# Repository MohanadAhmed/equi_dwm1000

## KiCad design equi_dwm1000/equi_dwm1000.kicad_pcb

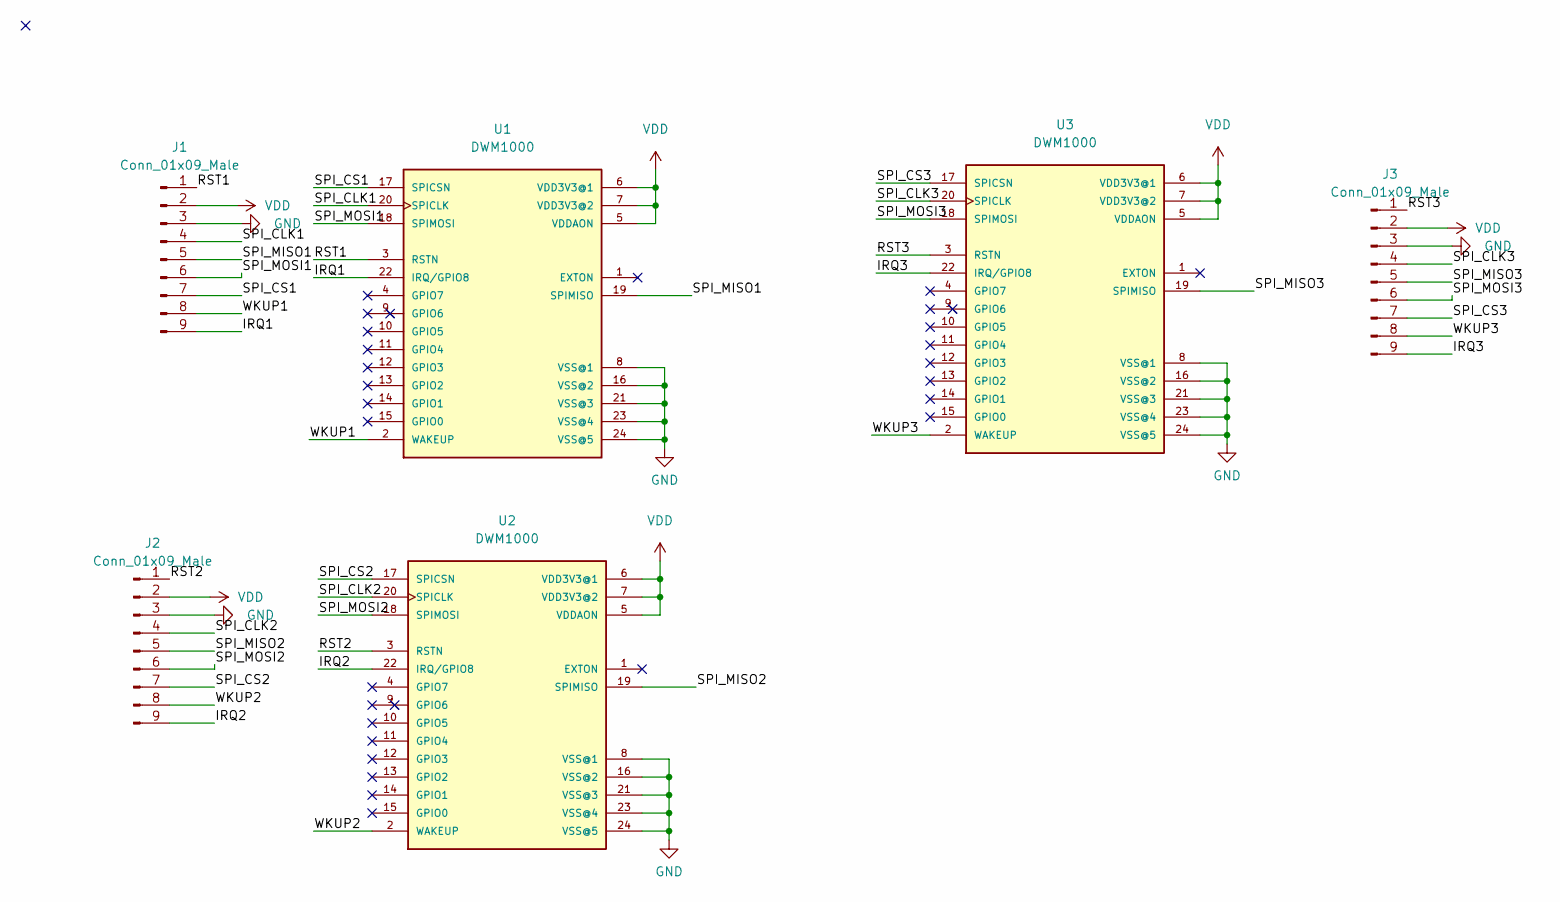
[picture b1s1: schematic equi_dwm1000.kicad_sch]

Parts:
J1, J2, J3: Conn_01x09_Male; PinHeader_1x09_P2.54mm_Vertical
U1, U2, U3: DWM1000

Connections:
/IRQ1: J1.9, U1.22 (IRQ/GPIO8)
/IRQ2: J2.9, U2.22 (IRQ/GPIO8)
/IRQ3: J3.9, U3.22 (IRQ/GPIO8)
/RST1: J1.1, U1.3 (RSTN)
/RST2: J2.1, U2.3 (RSTN)
/RST3: J3.1, U3.3 (RSTN)
/SPI_CLK1: J1.4, U1.20 (SPICLK)
/SPI_CLK2: J2.4, U2.20 (SPICLK)
/SPI_CLK3: J3.4, U3.20 (SPICLK)
/SPI_CS1: J1.7, U1.17 (SPICSN)
/SPI_CS2: J2.7, U2.17 (SPICSN)
/SPI_CS3: J3.7, U3.17 (SPICSN)
/SPI_MISO1: J1.5, U1.19 (SPIMISO)
/SPI_MISO2: J2.5, U2.19 (SPIMISO)
/SPI_MISO3: J3.5, U3.19 (SPIMISO)
/SPI_MOSI1: J1.6, U1.18 (SPIMOSI)
/SPI_MOSI2: J2.6, U2.18 (SPIMOSI)
/SPI_MOSI3: J3.6, U3.18 (SPIMOSI)
/WKUP1: J1.8, U1.2 (WAKEUP)
/WKUP2: J2.8, U2.2 (WAKEUP)
/WKUP3: J3.8, U3.2 (WAKEUP)
GND: J1.3, J2.3, J3.3, U1.8 (VSS@1), U1.16 (VSS@2), U1.21 (VSS@3), U1.23 (VSS@4), U1.24 (VSS@5), U2.8 (VSS@1), U2.16 (VSS@2), U2.21 (VSS@3), U2.23 (VSS@4), U2.24 (VSS@5), U3.8 (VSS@1), U3.16 (VSS@2), U3.21 (VSS@3), U3.23 (VSS@4), U3.24 (VSS@5)
VDD: J1.2, J2.2, J3.2, U1.5 (VDDAON), U1.6 (VDD3V3@1), U1.7 (VDD3V3@2), U2.5 (VDDAON), U2.6 (VDD3V3@1), U2.7 (VDD3V3@2), U3.5 (VDDAON), U3.6 (VDD3V3@1), U3.7 (VDD3V3@2)

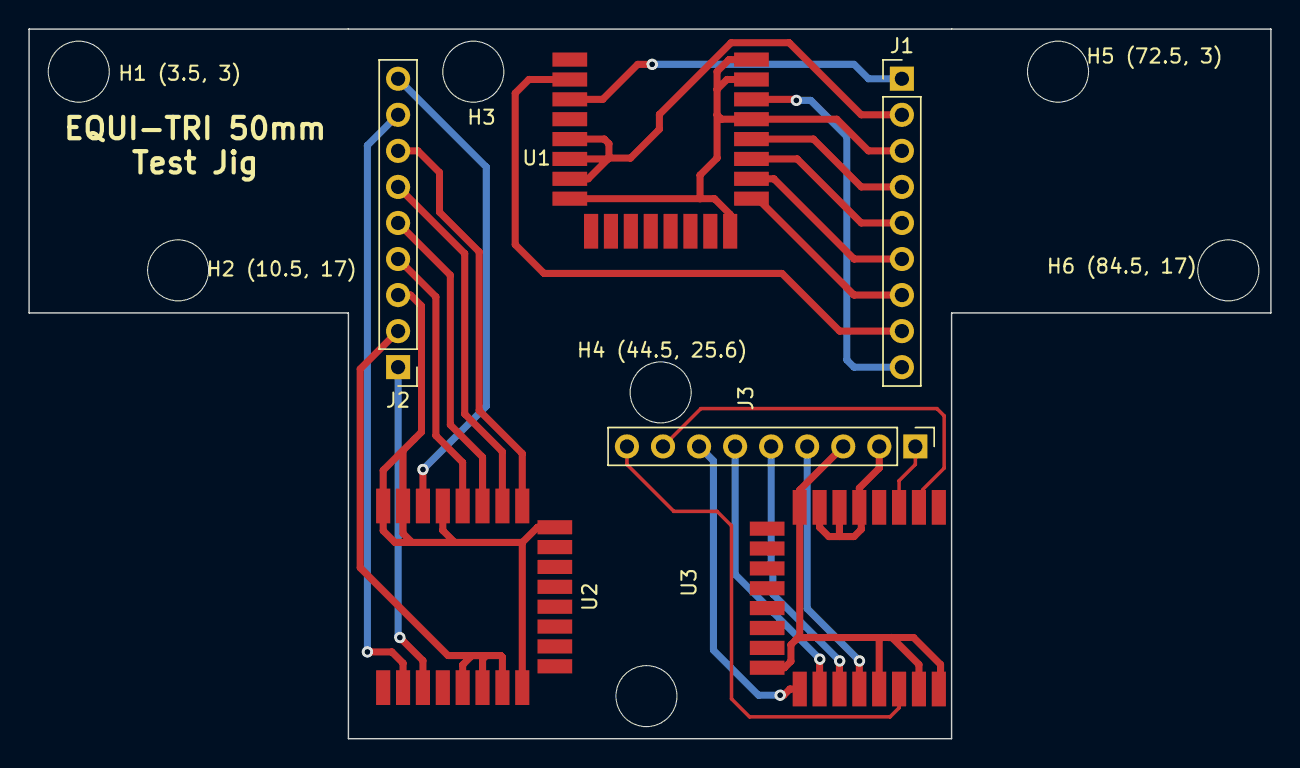
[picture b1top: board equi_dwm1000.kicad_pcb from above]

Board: 2 copper layers, 87.5 x 50.0 mm, 6 parts (0 on the bottom side), 23 nets.

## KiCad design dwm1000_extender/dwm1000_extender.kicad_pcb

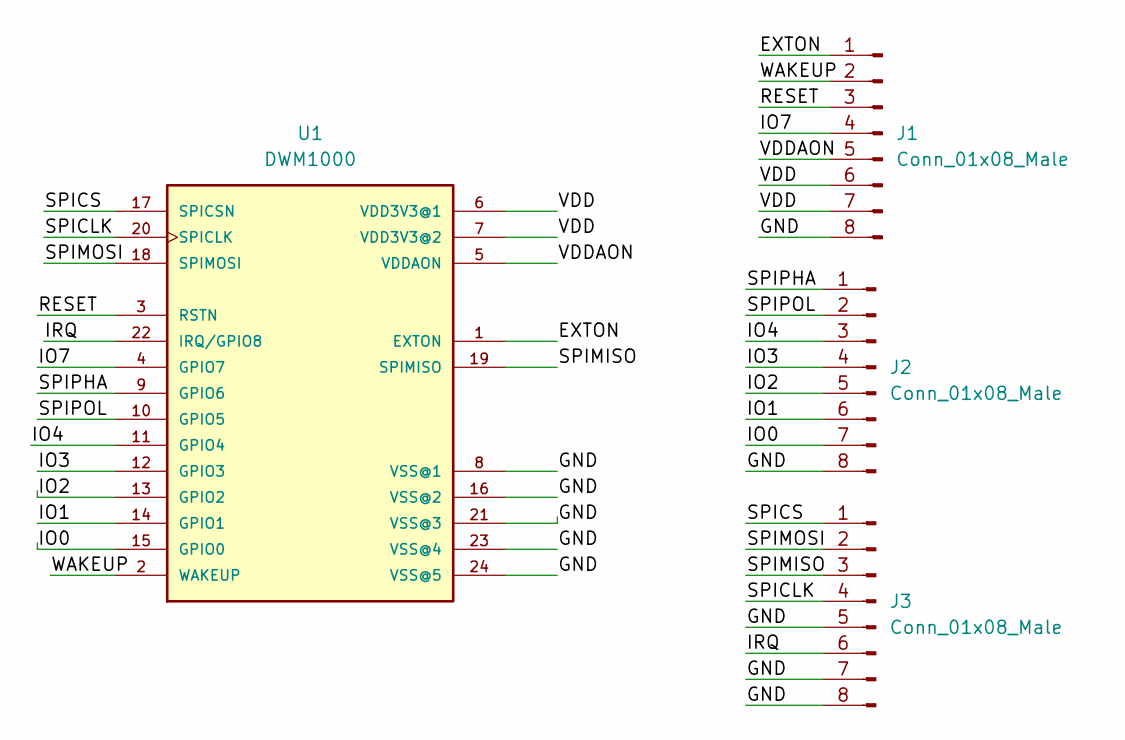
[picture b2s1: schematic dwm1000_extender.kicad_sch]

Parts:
J1, J2, J3: Conn_01x08_Male; PinHeader_1x08_P2.54mm_Vertical
U1: DWM1000

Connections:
/EXTON: J1.1, U1.1 (EXTON)
/GND: J1.8, J2.8, J3.5, J3.7, J3.8, U1.8 (VSS@1), U1.16 (VSS@2), U1.21 (VSS@3), U1.23 (VSS@4), U1.24 (VSS@5)
/IO0: J2.7, U1.15 (GPIO0)
/IO1: J2.6, U1.14 (GPIO1)
/IO2: J2.5, U1.13 (GPIO2)
/IO3: J2.4, U1.12 (GPIO3)
/IO4: J2.3, U1.11 (GPIO4)
/IO7: J1.4, U1.4 (GPIO7)
/IRQ: J3.6, U1.22 (IRQ/GPIO8)
/RESET: J1.3, U1.3 (RSTN)
/SPICLK: J3.4, U1.20 (SPICLK)
/SPICS: J3.1, U1.17 (SPICSN)
/SPIMISO: J3.3, U1.19 (SPIMISO)
/SPIMOSI: J3.2, U1.18 (SPIMOSI)
/SPIPHA: J2.1, U1.9 (GPIO6)
/SPIPOL: J2.2, U1.10 (GPIO5)
/VDD: J1.6, J1.7, U1.6 (VDD3V3@1), U1.7 (VDD3V3@2)
/VDDAON: J1.5, U1.5 (VDDAON)
/WAKEUP: J1.2, U1.2 (WAKEUP)

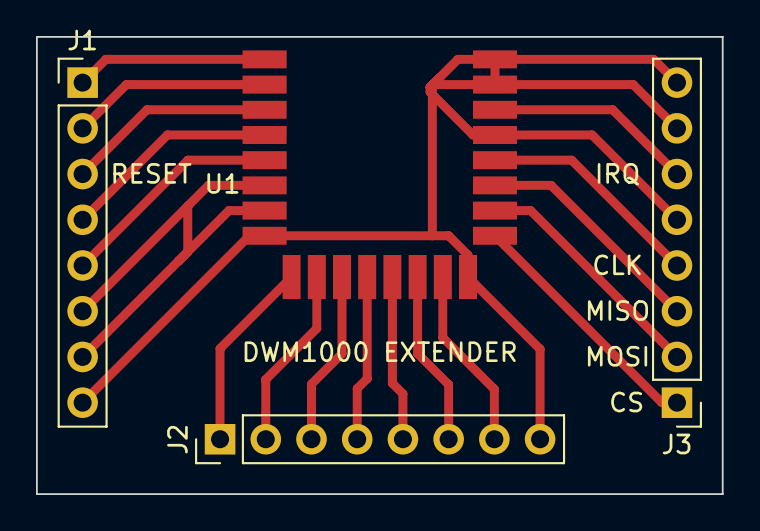
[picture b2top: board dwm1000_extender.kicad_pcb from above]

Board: 2 copper layers, 38.1 x 25.4 mm, 4 parts (0 on the bottom side), 19 nets.
